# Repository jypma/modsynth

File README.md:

# Eurorack modules collection

This repository contains a collection of eurorack module open hardware designs. It is a combination of designs found elsewhere (with references where relevant), and designs by me.

All schematics and boards are in Kicad format, and schematics, board and gerber exports are automated using KiBot and docker (see [export.sh](export.sh)).

## Modules

The following modules are available:

* A [AS3340-based oscillator](AS3340-VCO) designed by me (based on a combination of earlier designs from the internet)
* A [PT2399-based delay](PT2399-Delay) designed by me (based on a combination of earlier designs from the internet)
- A [Dual 4-channel mixer](DualMixer) module designed by me (based on basic opamp mixer essentials)
- A [Quad Attenuverter](QuadAttenuverter) with offset, based on an internet design
- [Ornament & Crime](OrnamentCrime), a well-known open hardware design
- Ray Wilson's  [Dual-VCA](RayWilson-Dual-VCA) as originally designed by Gerbrand Sterrenburg
- [Roland System 100 ADSR](SCM-140-ADSR) as originally designed by Gerbrand Sterrenburg
- The YUSynth [Steiner VCF](Steiner-VCF) as originally designed by Gerbrand Sterrenburg
- Music Thing Modular's [Turing Machine](TuringMachine), a well-known open hardware design

## Utilities

- A 16-bin [DIP to SOIC](adapter-soic16) adapter board (to mount SOIC chips on DIP sockets)
- A [Power distribution board](power-board) for eurorack modules

## Combined bill of material and shopping list

I'm maintaining a merged [bill of material](bom.org) for all modules, with component lists in stock at time of writing.

The only exception is the Teensy 3.0 / 3.1 / 3.2 required for _Ornament & Crime_. Those are impossible to find at the moment (I happen to have some, hence it's on the list).

# Generating BOM, gerbers, and pictures

The script `export.sh` in the root of the project will generate or update the artifacts in the  `export/` directory, such as BOMs, gerber files, packages, and various documentation pictures. Most of these files are not version-controlled (but those linked from the markdown documentation are).

Whenever changing a schematic, the export script will update the relevant pictures and artifacts. Re-exporting the same schematic will result in the same picture, so `git` plays nice with this.

## Link for simulation of triangle to sine converter

[here](https://falstad.com/circuit/circuitjs.html?ctz=CQAgjCAMB0l3BWK0AckDMYwE4As3sA2SQgdgCYFsQFIaa6EBTAWiwCgAlEXOEciiHTpC-QXXQ8+SOrOgJ2YUrh7pyY9QjDqB6iGHh8YudJFIhOAewCuAOwAm7AO5S6u1TvHsATjXIoNPwD0BHU3cjh2AHMgoVDY9BQVWXYAFxpiQMJyFXc6CBZcaFJabWylCu1JGARCBDUwFFI8BF5cclEDOnsmADMAQ2sAG1TnDLdBUIC8nxBs3Jy5xbBcZPBDLiWVbQD5kCIoQ95wMMOasb2drfBVqAvF8kW9ylFIWcJj-wDSSFyUAIk2DeShUHwkIhAPxUwk66yM8gsTAAzgBLJGpfq2ADGTAuxxhc0+-zuLjB-GJz2JbxcUKEENpXzuvjI6kSoMEqwB-A2pMEbLmfIid3SaAm6lIhGm4nAIEKxUIYFCuHq2S0cFe8ioCAo+GU2CUyk6fB6A2GoxpkvJ31+VqZIBQYFEphUDqdlvCkRirqElu9vFkJPtjqENu9MxcYcEosCb18Eumi3j4Ey+Q23CTVyTBwDx20Z2QCgtAUzlsdKSL-ETlped141BQB0ZXWmxIgMFEbDAqBQrQ+P3IitwxHMMEg5Ewtcg1CwNudJz4c7b0A7Bmg6FIphyiuIpgII9g47bmzwuVq+1ujzWdFzpzkCm4WHi7kfOmOOfyt4Lx9uajoJ7in7HGwn7nA+iqshCL4+ly150MB+bnL4DadBK+zYHoqGpvAYzIeAqG4eGaEYUakDFphYzNnhJEtgCOGNlGaAxjhjHuP8bhvsx7F0M8izUpC1aLEkCbJDhuDCfaYkhiJEaSXOuFzrG9qMf6Sngq8cKRBGjEEvJNpvF6yl8GxHhnLMBgPK2pE0YcXSaesxJNgYfy0S45nOXC1mKVgQpKJ0ET5Jh4C0HZ3kBZ0TlUYGM7bKh0W2nx2h8L584SHp0T2cEPlWQBpmudlv7gBFBVvAA8ilUknLJel3NwLI8JJdViQGsGynmzXyGMTX8GeXWXoGvWLFMlbSbEfVDTMlgZDwRwoIQRrIG29DNUIcyHE67BAA)

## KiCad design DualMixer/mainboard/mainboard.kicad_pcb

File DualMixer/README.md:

# Dual 4-channel mixer

Based off a variety of simple opamp circuits, with the following design goals:

- 4 inputs per mixer
- Individual buffers for each input, to limit cross-talk between connected oscillators
- As close to unity output when one input connected and fully opened (hence, output A can be connected to input B1 for a 7-channel mixer)
- Peak LED for each output

## Main board

### Schematic

### PCB

## IO Board

### Schematic

### PCB

## Face plate

# Simulation

Simulate this circuit on [circuitjs](https://falstad.com/circuit/circuitjs.html?ctz=CQAgjCAMB0l3BWEAOM0CcAmSAWMA2SAdn3xLCQUhEuoQFMBaMMAKB0nRB3xxAGZsNQgKH8o0fCGb9omHOhyYE-fkXSQw6FhMiZ+YeEeN6orAEo0wmEJmTIrNzERvVqHcK6gSEFxwIQbBGsBfAc3bmpmLzdoX0t+XAEk+WpEvmoIQzgab1jfAHdkvnTuXmKzIp4S-ikcQQFayu4G1TqG+tdWKo6GhBIWrqL+9qCBwTdumnGhBBEJswAnaakFshsFtMS4PyJA0Ic9jeQM7w9ovJ9d-dKj23tLjxCImF8OLiIktpQc7-EYKQyaAuQjITAETDoBDIIiqXT6bImYxDECfEpCdaiSbLZCtJq4mx4KSZDjwVg4joEFAddDE7ifHYAc2phNpLP8kyKBMaUmQvyakCm3KJIDCDhFgqKYu4VOl-H2ktFD3lNjRARR3O+yDZ30FAHkUDqmlgHLqzAATdlahrOJzgAByeBwyCFNpc7Ow4VdTkgDm0Pq9AGMQP7bL6QyFbd40EjY2AmEQaJINPoYRQ4NYwOFYJpySGBp781Io9RMNgyUVQ4X0AXw4LmVX3VWHpMGwWmwWW2Z3uA4A4tDYWEkB+AJID9BgFIQs2B+Cd1ImYHoDLHkWZLIY5uARJupGAcKd3JkYlcN5At2W+LvbB4Iudnnk4lNsg5q7Wvct0FhwAMTT+6YiOyft+YC-t+bKZMYrANnY-6GnuAzYuAhhXiBWaoV4ZY7BCyEnOAIHyP2342Oa9AAGYAIYAK4ADYAC6MDR9CWhALywGwzLWM6+GDoRN4vHmIzcGymJTmcDKKpiazumJ9YrMJUgIAeCl5NB8lKXwGk0MpSFCVpmJae4EmCQMCDfgZ35GWSzJ6d+WlmTEUyiSJ7qGU5rnKRZKIvnBX6DohrAAPa2OIrHcMgpBhhIYVXiUth0pgqysEAA)

# Notes for boards v1 (Obsolete)

The level pots go in the wrong direction. Fix: Mount I/O board the wrong way, and connect the unconnected top left pin of the dual header row to its right sibling(ground). This will reverse the A/B output LEDs, but that's fine.

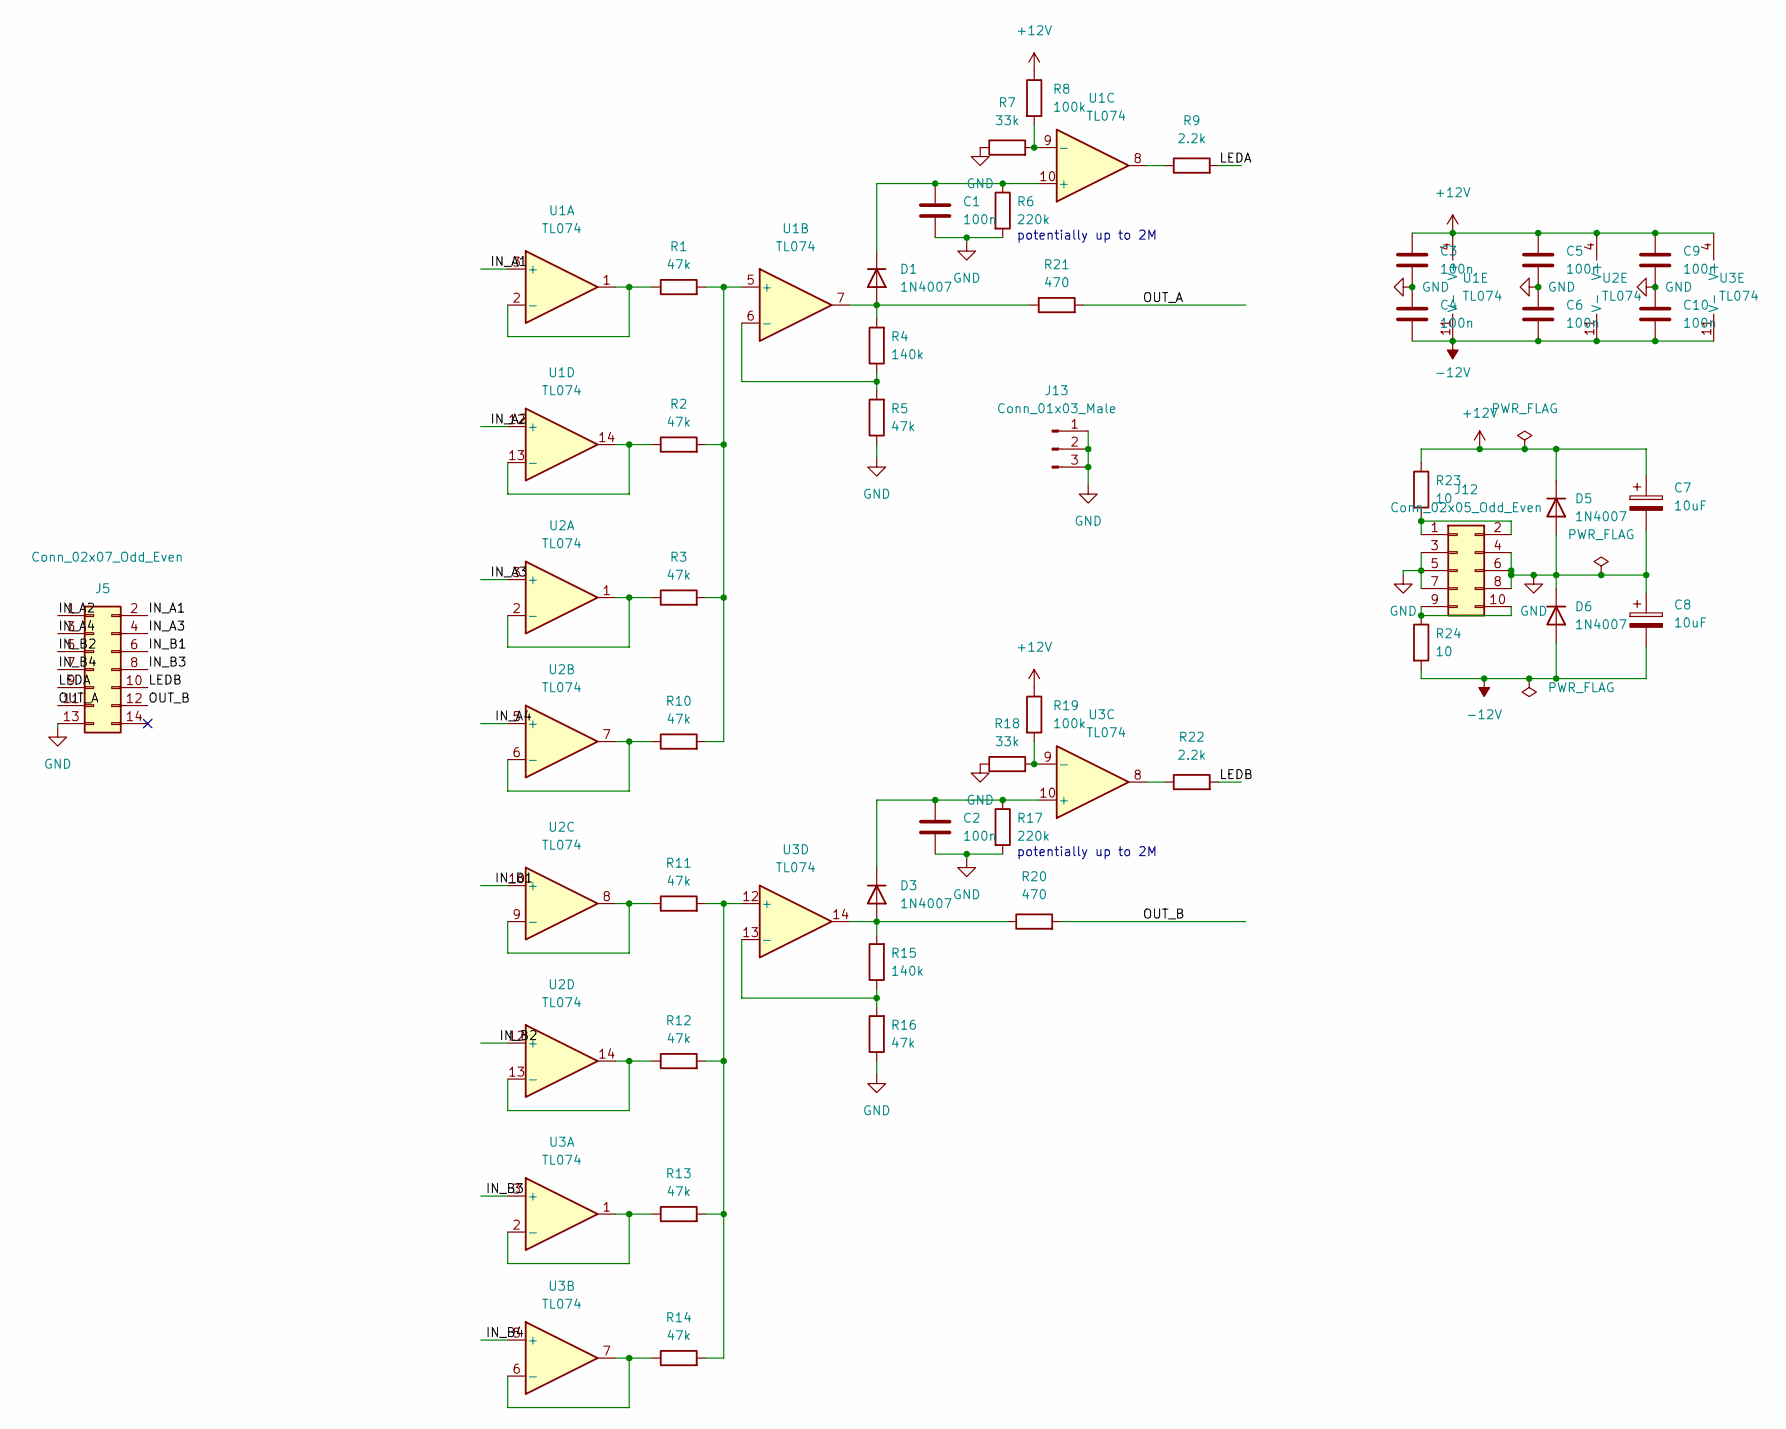
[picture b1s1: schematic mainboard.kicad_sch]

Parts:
C1, C2, C3, C4, C5, C6, C9, C10: 100n; C_0603_1608Metric_Pad1.08x0.95mm_HandSolder
C7, C8: 10uF; CP_Radial_D5.0mm_P2.50mm
D1, D3, D5, D6: 1N4007; D_DO-41_SOD81_P7.62mm_Horizontal
J5: Conn_02x07_Odd_Even; PinHeader_2x07_P2.54mm_Vertical
J12: Conn_02x05_Odd_Even; PinHeader_2x05_P2.54mm_Vertical
J13: Conn_01x03_Male; PinHeader_1x03_P2.54mm_Vertical
R1, R2, R3, R5, R10, R11, R12, R13, R14, R16: 47k; R_0603_1608Metric_Pad0.98x0.95mm_HandSolder
R4, R15: 140k; R_0603_1608Metric_Pad0.98x0.95mm_HandSolder
R6, R17: 220k; R_0603_1608Metric_Pad0.98x0.95mm_HandSolder
R7, R18: 33k; R_0603_1608Metric_Pad0.98x0.95mm_HandSolder
R8, R19: 100k; R_0603_1608Metric_Pad0.98x0.95mm_HandSolder
R9, R22: 2.2k; R_0603_1608Metric_Pad0.98x0.95mm_HandSolder
R20, R21: 470; R_0603_1608Metric_Pad0.98x0.95mm_HandSolder
R23, R24: 10; R_0603_1608Metric_Pad0.98x0.95mm_HandSolder
U1, U2, U3: TL074; SO-14_3.9x8.65mm_P1.27mm

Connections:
+12V: C3.1, C5.1, C7.1, C9.1, D5.1 (K), R8.1, R19.1, R23.1, U1.4 (V+), U2.4 (V+), U3.4 (V+)
-12V: C4.2, C6.2, C8.2, C10.2, D6.2 (A), R24.2, U1.11 (V-), U2.11 (V-), U3.11 (V-)
/IN_A1: J5.2, U1.3 (+)
/IN_A2: J5.1, U1.12 (+)
/IN_A3: J5.4, U2.3 (+)
/IN_A4: J5.3, U2.5 (+)
/IN_B1: J5.6, U2.10 (+)
/IN_B2: J5.5, U2.12 (+)
/IN_B3: J5.8, U3.3 (+)
/IN_B4: J5.7, U3.5 (+)
/LEDA: J5.9, R9.2
/LEDB: J5.10, R22.2
/OUT_A: J5.11, R21.2
/OUT_B: J5.12, R20.2
GND: C1.2, C2.2, C3.2, C4.1, C5.2, C6.1, C7.2, C8.1, C9.2, C10.1, D5.2 (A), D6.1 (K), J5.13, J12.3, J12.4, J12.5, J12.6, J12.7, J12.8, J13.1, J13.2, J13.3, R5.1, R6.2, R7.1, R16.1, R17.2, R18.1
unnamed: D1.2 (A), R4.2, R21.1, U1.7
unnamed: C1.1, D1.1 (K), R6.1, U1.10 (+)
unnamed: D3.2 (A), R15.2, R20.1, U3.14
unnamed: C2.1, D3.1 (K), R17.1, U3.10 (+)
unnamed: J12.1, J12.2, R23.2
unnamed: J12.9, J12.10, R24.1
unnamed: R9.1, U1.8
unnamed: R22.1, U3.8
unnamed: R1.1, U1.1, U1.2 (-)
unnamed: R1.2, R2.2, R3.2, R10.2, U1.5 (+)
unnamed: R4.1, R5.2, U1.6 (-)
unnamed: R7.2, R8.2, U1.9 (-)
unnamed: R2.1, U1.13 (-), U1.14
unnamed: R3.1, U2.1, U2.2 (-)
unnamed: R10.1, U2.6 (-), U2.7
unnamed: R11.1, U2.8, U2.9 (-)
unnamed: R12.1, U2.13 (-), U2.14
unnamed: R13.1, U3.1, U3.2 (-)
unnamed: R14.1, U3.6 (-), U3.7
unnamed: R18.2, R19.2, U3.9 (-)
unnamed: R11.2, R12.2, R13.2, R14.2, U3.12 (+)
unnamed: R15.1, R16.2, U3.13 (-)

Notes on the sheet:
potentially up to 2M

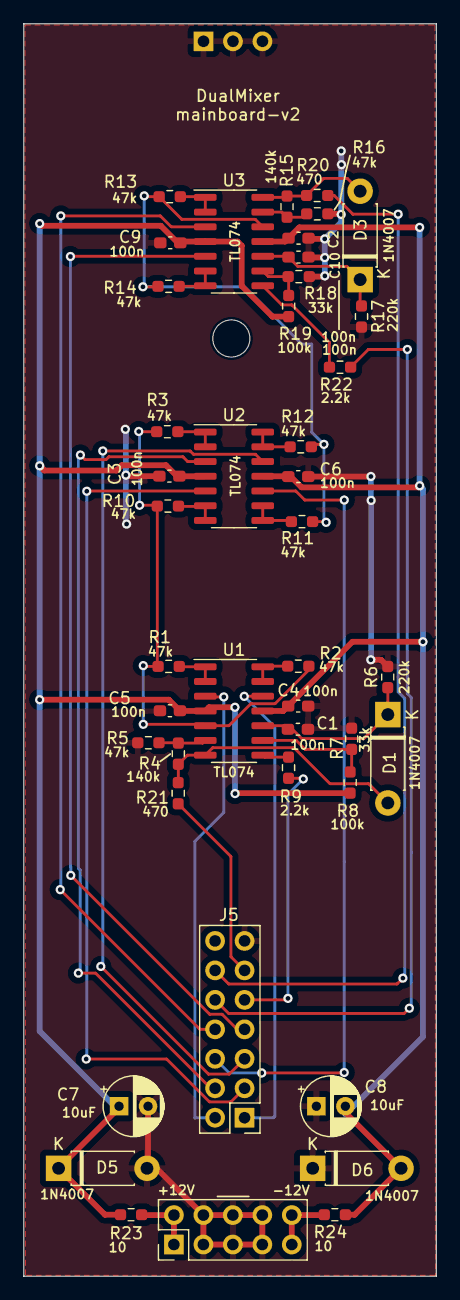
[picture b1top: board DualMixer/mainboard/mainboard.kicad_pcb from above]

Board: 2 copper layers, 35.6 x 107.9 mm, 44 parts (1 on the bottom side), 37 nets.

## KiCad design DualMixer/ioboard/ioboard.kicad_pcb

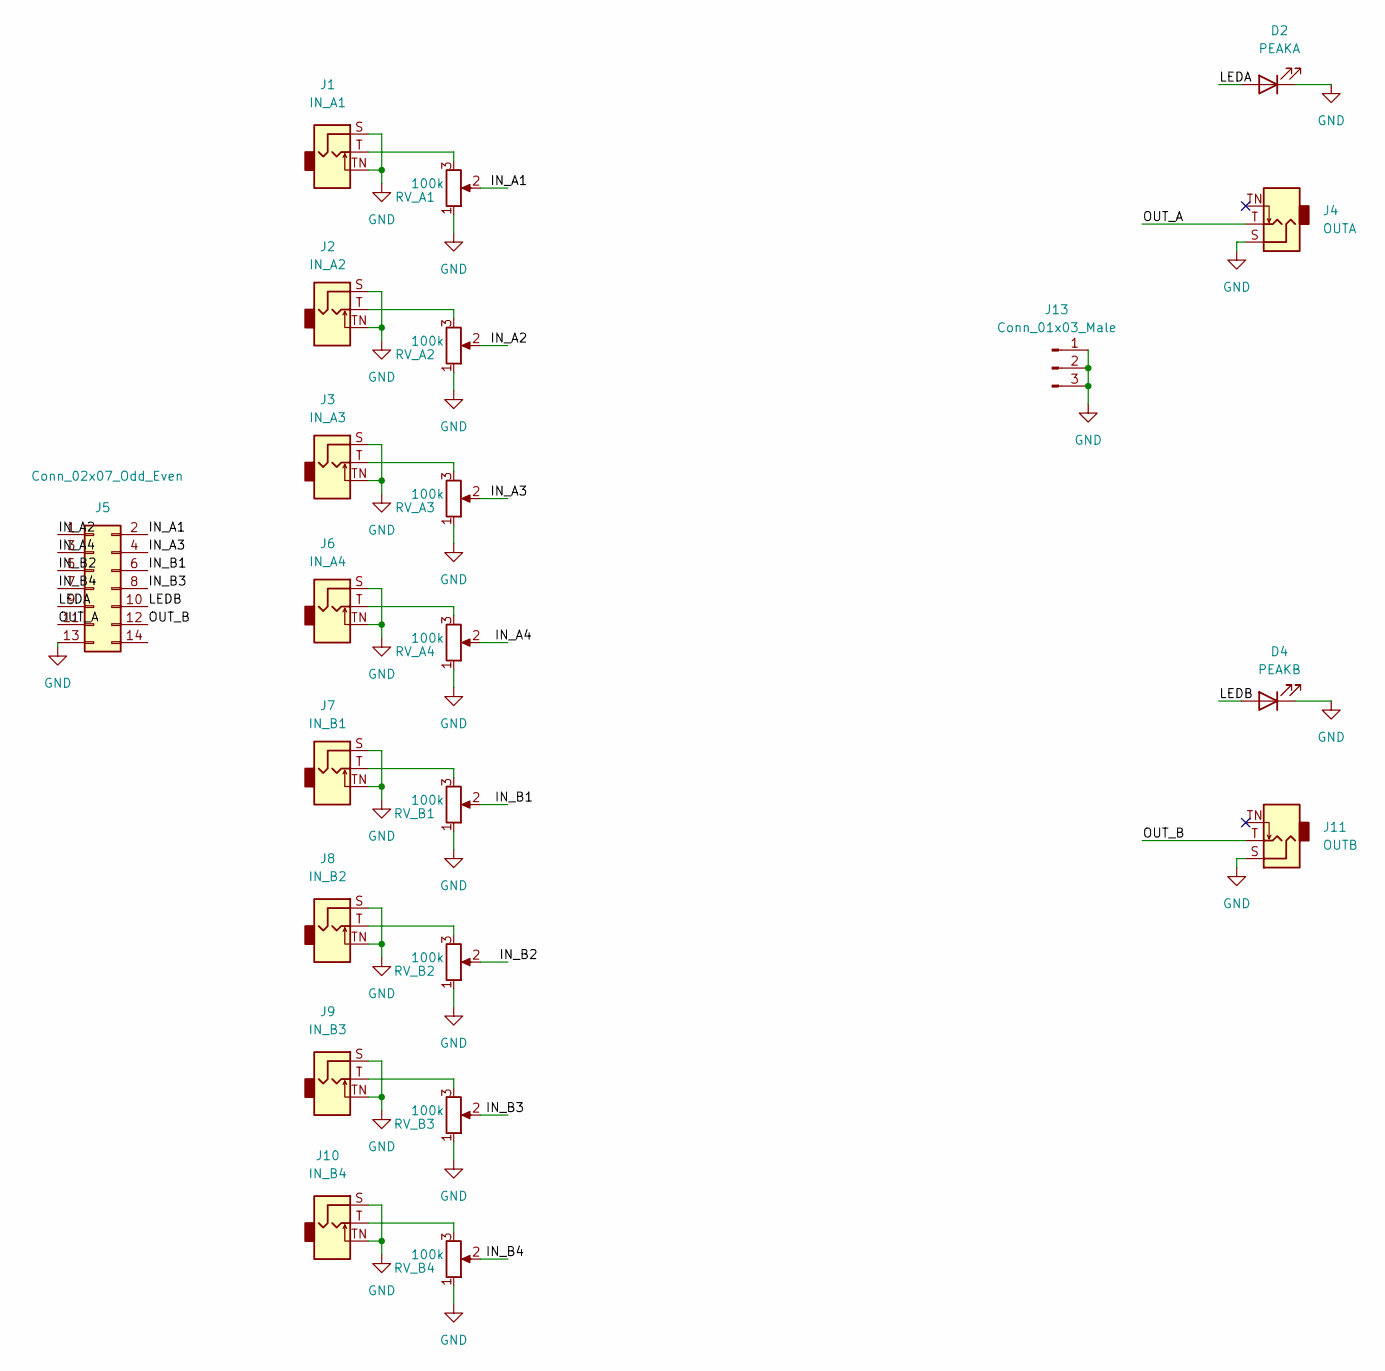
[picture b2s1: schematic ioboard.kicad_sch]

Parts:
D2: PEAKA; LED_D3.0mm
D4: PEAKB; LED_D3.0mm
J1: IN_A1; Jack_3.5mm_QingPu_WQP-PJ398SM_Vertical_CircularHoles
J2: IN_A2; Jack_3.5mm_QingPu_WQP-PJ398SM_Vertical_CircularHoles
J3: IN_A3; Jack_3.5mm_QingPu_WQP-PJ398SM_Vertical_CircularHoles
J4: OUTA; Jack_3.5mm_QingPu_WQP-PJ398SM_Vertical_CircularHoles
J5: Conn_02x07_Odd_Even; PinHeader_2x07_P2.54mm_Vertical
J6: IN_A4; Jack_3.5mm_QingPu_WQP-PJ398SM_Vertical_CircularHoles
J7: IN_B1; Jack_3.5mm_QingPu_WQP-PJ398SM_Vertical_CircularHoles
J8: IN_B2; Jack_3.5mm_QingPu_WQP-PJ398SM_Vertical_CircularHoles
J9: IN_B3; Jack_3.5mm_QingPu_WQP-PJ398SM_Vertical_CircularHoles
J10: IN_B4; Jack_3.5mm_QingPu_WQP-PJ398SM_Vertical_CircularHoles
J11: OUTB; Jack_3.5mm_QingPu_WQP-PJ398SM_Vertical_CircularHoles
J13: Conn_01x03_Male; PinHeader_1x03_P2.54mm_Vertical
RV_A1, RV_A2, RV_A3, RV_A4: 100k; Potentiometer_Alps_RK09K_Single_Vertical
RV_B1, RV_B2, RV_B3, RV_B4: 100k; Potentiometer_Alps_RK09K_Single_Vertical

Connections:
/IN_A1: J5.2, RV_A1.2
/IN_A2: J5.1, RV_A2.2
/IN_A3: J5.4, RV_A3.2
/IN_A4: J5.3, RV_A4.2
/IN_B1: J5.6, RV_B1.2
/IN_B2: J5.5, RV_B2.2
/IN_B3: J5.8, RV_B3.2
/IN_B4: J5.7, RV_B4.2
/LEDA: D2.2 (A), J5.9
/LEDB: D4.2 (A), J5.10
/OUT_A: J4.T, J5.11
/OUT_B: J5.12, J11.T
GND: D2.1 (K), D4.1 (K), J1.S, J1.TN, J2.S, J2.TN, J3.S, J3.TN, J4.S, J5.13, J6.S, J6.TN, J7.S, J7.TN, J8.S, J8.TN, J9.S, J9.TN, J10.S, J10.TN, J11.S, J13.1, J13.2, J13.3, RV_A1.1, RV_A2.1, RV_A3.1, RV_A4.1, RV_B1.1, RV_B2.1, RV_B3.1, RV_B4.1
unnamed: J1.T, RV_A1.3
unnamed: J2.T, RV_A2.3
unnamed: J3.T, RV_A3.3
unnamed: J6.T, RV_A4.3
unnamed: J7.T, RV_B1.3
unnamed: J8.T, RV_B2.3
unnamed: J9.T, RV_B3.3
unnamed: J10.T, RV_B4.3

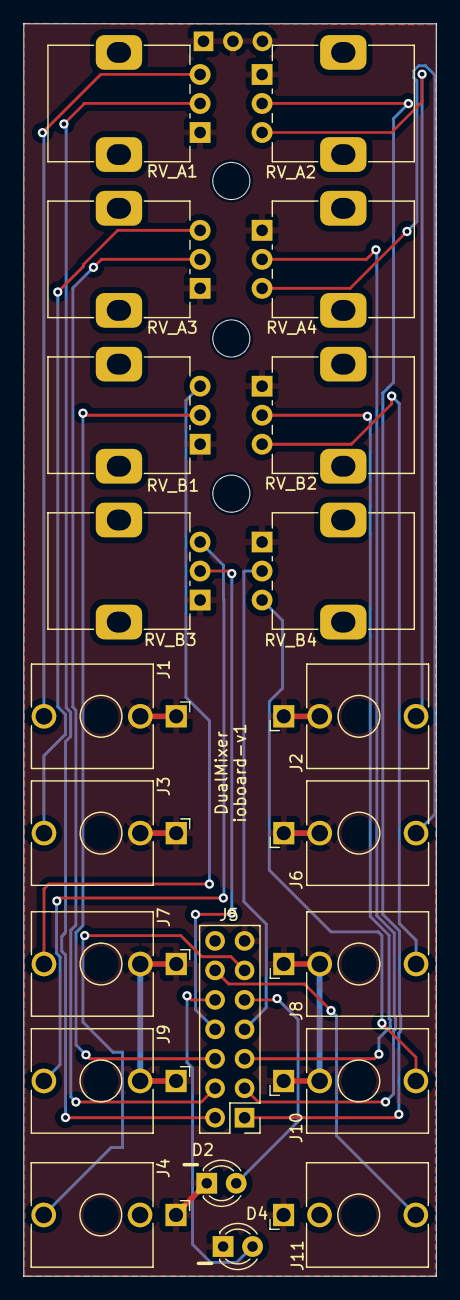
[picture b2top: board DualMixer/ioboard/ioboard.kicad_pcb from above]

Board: 2 copper layers, 35.6 x 107.9 mm, 22 parts (1 on the bottom side), 21 nets.

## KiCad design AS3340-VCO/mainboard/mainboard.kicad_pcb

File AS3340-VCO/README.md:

# AS3340 VCO

This design is a VCO based on the AS3340 chip, built up from a combination of designs found on the internet, resulting in the following features:
- Compact size
- Octave selector
- Holds tuning over time and temperature
* Precise finetune by note
* The usual linear FM, exponential FM and PWM inputs

## Main board

### Schematic

### PCB

## IO Board

### Schematic

### PCB

## Face plate

# Calibration
- Set to lowest octave
- Tune knob to lowest (1)
- Turn off LFO mode
- Set PWM to middle
- Connect V meter between GND and 1V
- Tweak RV_1V so we get 1.000V
- Connect V meter between GND and 7V
- Tweak RV_7V so we get about 7V
- Connect mV meter between TP1 and TP2
- Tweak RV_TEMPCO until voltage is 0V
- Put in JP1 to get a stable frequency
- Observe the triangle or square output
- Tweak RV_REF_PITCH_C6 until pitch is C6 (1046.5 Hz)
- Observe the sine output
- Tweak RV_OFFSET so that the middle value is 0V
- Tweak RV_SYM and RV_ROUND so the sine looks good
- Remove JP1
- Apply +5.000V CV
- Tweak RV_REFIND_C6 until pitch is again C6 (1046.5 Hz)
- Applu 0.000V CV
- Tweak RV_SCALE until pitch is 32.7Hz
- Connect V meter between GND and 1V
- Tweak RV_1V so we get 1.000V (TODO: figure out why this drifts)
- Connect V meter between GND and 7V
- Set to octave 6
- Tweak RV_7V until pitch is again C6 (1046.5 Hz)

# Old notes on advanced tuning schematic

## Tune towards C6
- 1M8: max ~800Hz
- 1M6: max ~910Hz
- 1M3: Spot on.
- Option: Replace 1M8 with 1M + 1M trimmer. But probably just a 0603 pad is fine too, we'll replace it with a fixed value for the main cap we end up using.

- Add an LFO switch, which adds a capacitor in parallel to the 1nF main cap.
  * normal labels: C1 through C9
  * 470 nF -> x labels:   13s   6.5s    3.2s    1.5s     0.78s      0.38s    0.19s   0.094s

- Octave switch goes from 0V to 7V (8 position switch, 7x10k 0.1% between the 8 positions. Make 7V with a TL431, R1 is 10k, R1 is 10k + 10k pot, 1k series resistor, plus 100nF bypass). Test point at +5V.
- Need a buffer opamp after the octave switch, even with the TL431 in front. TL072 with +12/-12V supply.

- Fine tune goes from 0V to 1V (take 7V from the octave switch, through 470k + 200k trimmer, to 100k pot).
- Need a buffer opamp after the fine tune as well.

- Put the high frequency tracking in the schematic, but don't need to initially populate.

# Errors in rev1 boards (obsolete)

- Mainboard silkscreen has the positions of values for R28 and R31 swapped. R28 should be 30k, and R31 should be 10k.
- Mainboard R41 should not have been to ground, it should be to -12V instead. Solder it to the left pad only (pointing left), and wire the other terminal to the bottom of R7 (which is -12V).
- IO board tune pot hole needs to be 7mm, to accommodate pots that are mounted

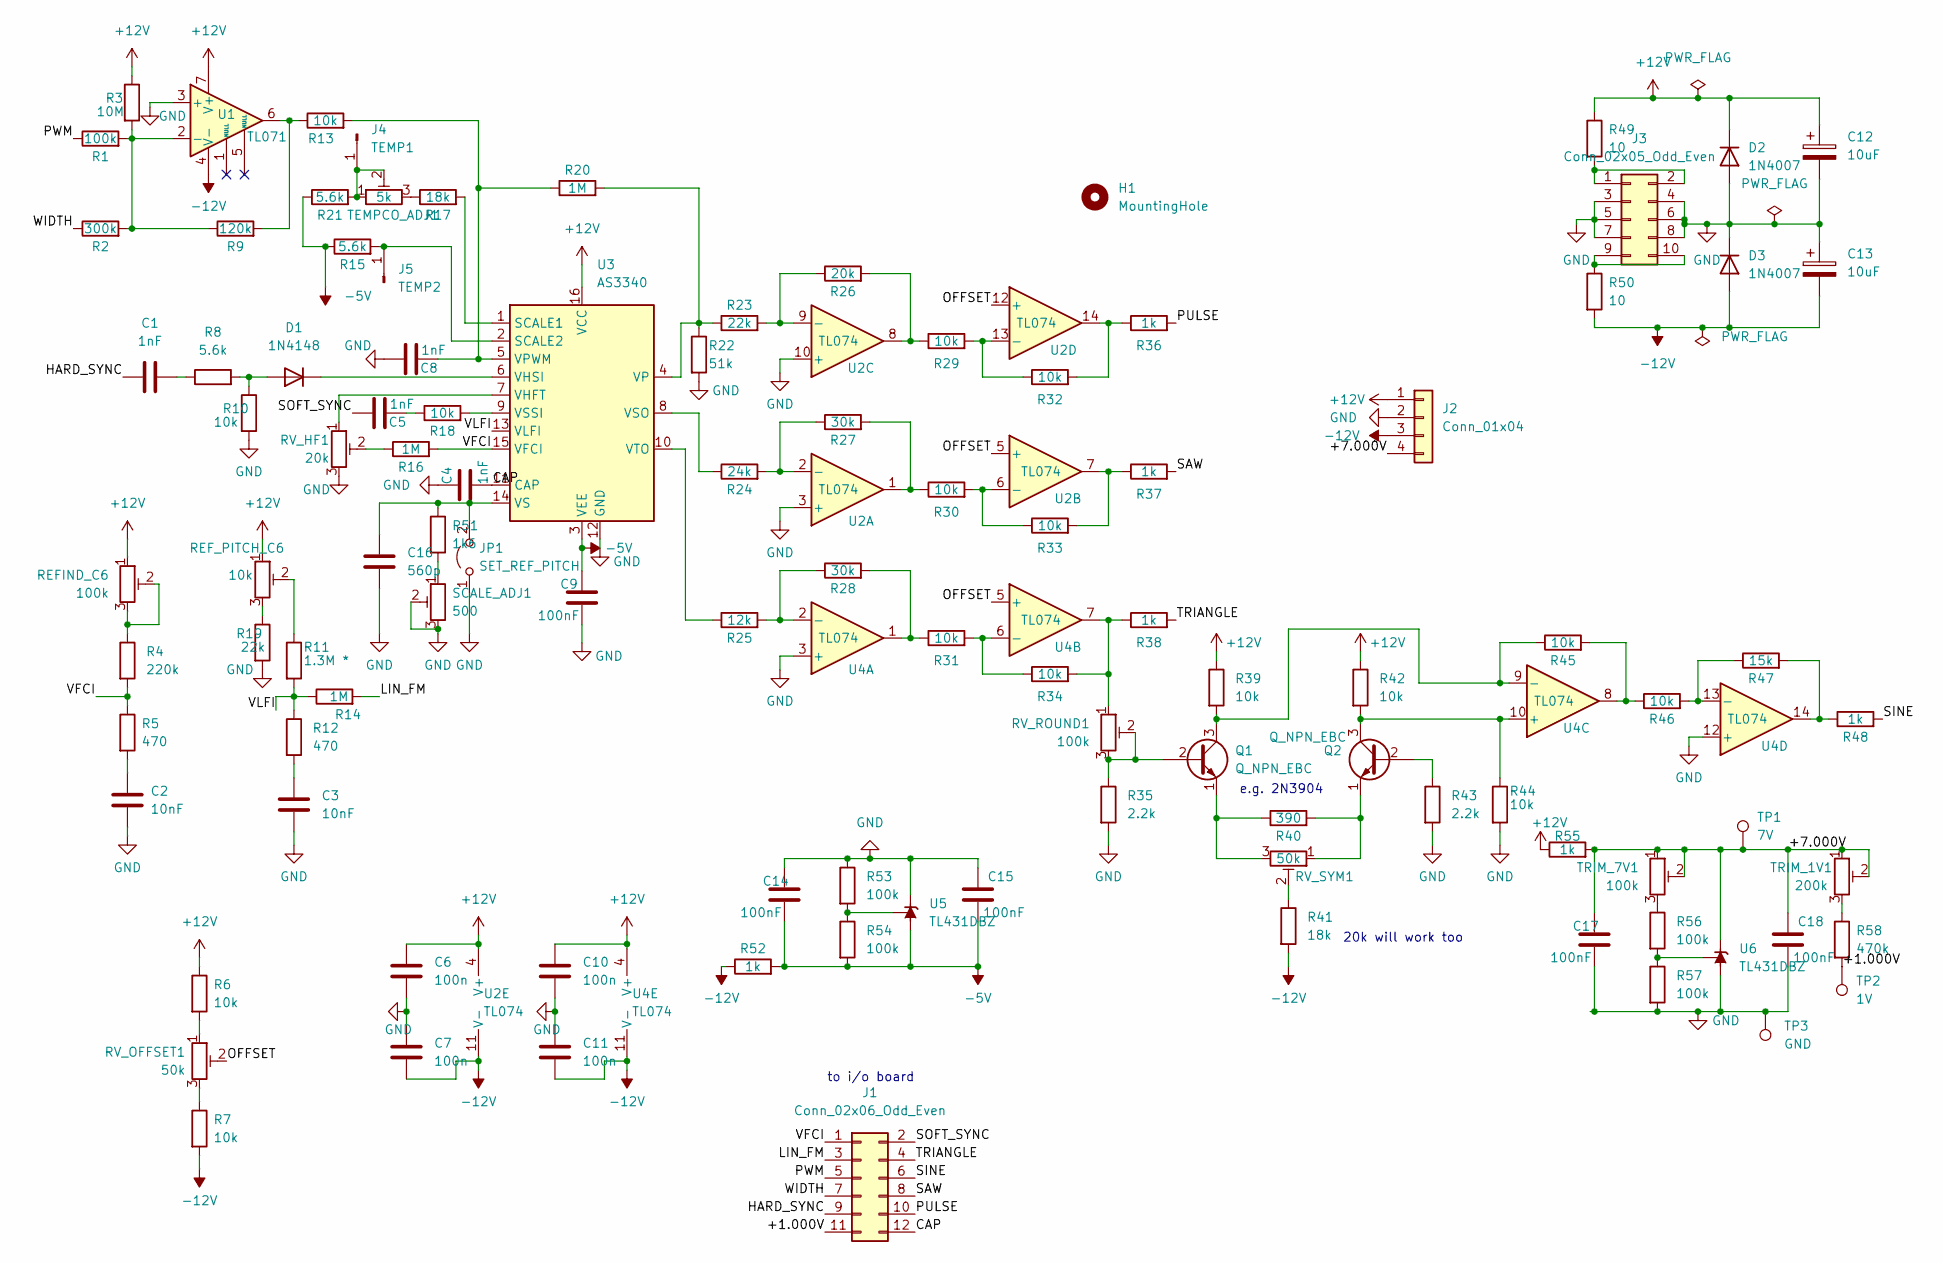
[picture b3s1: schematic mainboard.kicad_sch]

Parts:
C1, C5, C8: 1nF; C_0603_1608Metric_Pad1.08x0.95mm_HandSolder
C2, C3: 10nF; C_0603_1608Metric_Pad1.08x0.95mm_HandSolder
C4: 1nF; C_Rect_L7.0mm_W3.5mm_P5.00mm
C6, C7, C10, C11: 100n; C_0603_1608Metric_Pad1.08x0.95mm_HandSolder
C9, C14, C15, C17, C18: 100nF; C_0603_1608Metric_Pad1.08x0.95mm_HandSolder
C12, C13: 10uF; CP_Radial_D5.0mm_P2.50mm
C16: 560p; C_0603_1608Metric_Pad1.08x0.95mm_HandSolder
D1: 1N4148; D_DO-34_SOD68_P7.62mm_Horizontal
D2, D3: 1N4007; D_DO-41_SOD81_P7.62mm_Horizontal
H1: MountingHole; MountingHole_3.2mm_M3_NoCourt
J1: Conn_02x06_Odd_Even; PinHeader_2x06_P2.54mm_Vertical
J2: Conn_01x04; PinHeader_1x04_P2.54mm_Vertical
J3: Conn_02x05_Odd_Even; PinHeader_2x05_P2.54mm_Vertical
J4: TEMP1; PinHeader_1x01_P2.54mm_Vertical
J5: TEMP2; PinHeader_1x01_P2.54mm_Vertical
JP1: SET_REF_PITCH; PinHeader_1x02_P2.54mm_Vertical
Q1, Q2: Q_NPN_EBC; TO-92
R1, R53, R54, R56, R57: 100k; R_0603_1608Metric_Pad0.98x0.95mm_HandSolder
R2: 300k; R_0603_1608Metric_Pad0.98x0.95mm_HandSolder
R3: 10M; R_0603_1608Metric_Pad0.98x0.95mm_HandSolder
R4: 220k; R_0603_1608Metric_Pad0.98x0.95mm_HandSolder
R5, R12: 470; R_0603_1608Metric_Pad0.98x0.95mm_HandSolder
R6, R7, R10, R13, R18, R29, R30, R31, R32, R33, R34, R39, R42, R44, R45, R46: 10k; R_0603_1608Metric_Pad0.98x0.95mm_HandSolder
R8, R15, R21: 5.6k; R_0603_1608Metric_Pad0.98x0.95mm_HandSolder
R9: 120k; R_0603_1608Metric_Pad0.98x0.95mm_HandSolder
R11: 1.3M *; R_0603_1608Metric_Pad0.98x0.95mm_HandSolder
R14, R16, R20: 1M; R_0603_1608Metric_Pad0.98x0.95mm_HandSolder
R17, R41: 18k; R_0603_1608Metric_Pad0.98x0.95mm_HandSolder
R19, R23: 22k; R_0603_1608Metric_Pad0.98x0.95mm_HandSolder
R22: 51k; R_0603_1608Metric_Pad0.98x0.95mm_HandSolder
R24: 24k; R_0603_1608Metric_Pad0.98x0.95mm_HandSolder
R25: 12k; R_0603_1608Metric_Pad0.98x0.95mm_HandSolder
R26: 20k; R_0603_1608Metric_Pad0.98x0.95mm_HandSolder
R27, R28: 30k; R_0603_1608Metric_Pad0.98x0.95mm_HandSolder
R35, R43: 2.2k; R_0603_1608Metric_Pad0.98x0.95mm_HandSolder
R36, R37, R38, R48, R52, R55: 1k; R_0603_1608Metric_Pad0.98x0.95mm_HandSolder
R40: 390; R_0603_1608Metric_Pad0.98x0.95mm_HandSolder
R47: 15k; R_0603_1608Metric_Pad0.98x0.95mm_HandSolder
R49, R50: 10; R_0603_1608Metric_Pad0.98x0.95mm_HandSolder
R51: 1k6; R_0603_1608Metric_Pad0.98x0.95mm_HandSolder
R58: 470k; R_0603_1608Metric_Pad0.98x0.95mm_HandSolder
REFIND_C6: 100k; Potentiometer_Bourns_3266Y_Vertical
REF_PITCH_C6: 10k; Potentiometer_Bourns_3266Y_Vertical
RV_HF1: 20k; Potentiometer_Bourns_3266Y_Vertical
RV_OFFSET1: 50k; Potentiometer_Bourns_3266Y_Vertical
RV_ROUND1: 100k; Potentiometer_Bourns_3266Y_Vertical
RV_SYM1: 50k; Potentiometer_Bourns_3266Y_Vertical
SCALE_ADJ1: 500; Potentiometer_Bourns_3266Y_Vertical
TEMPCO_ADJ1: 5k; Potentiometer_Bourns_3266Y_Vertical
TP1: 7V; PinHeader_1x01_P2.54mm_Vertical
TP2: 1V; PinHeader_1x01_P2.54mm_Vertical
TP3: GND; PinHeader_1x01_P2.54mm_Vertical
TRIM_1V1: 200k; Potentiometer_Bourns_3266Y_Vertical
TRIM_7V1: 100k; Potentiometer_Bourns_3266Y_Vertical
U1: TL071; DIP-8_W7.62mm_Socket
U2, U4: TL074; SO-14_3.9x8.65mm_P1.27mm
U3: AS3340; DIP-16_W7.62mm_Socket
U5, U6: TL431DBZ; SOT-23

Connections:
+12V: C6.1, C10.1, C12.1, D2.1 (K), J2.1, R3.1, R6.1, R39.1, R42.1, R49.1, R55.1, REFIND_C6.1, REF_PITCH_C6.1, U1.7 (V+), U2.4 (V+), U3.16 (VCC), U4.4 (V+)
-5V: C9.1, C14.2, C15.2, R15.1, R21.1, R52.2, R54.2, U3.3 (VEE), U5.3 (A)
-12V: C7.2, C11.2, C13.2, D3.2 (A), J2.3, R7.2, R41.2, R50.2, R52.1, U1.4 (V-), U2.11 (V-), U4.11 (V-)
/+1.000V: J1.11, R58.2, TP2.1
/+7.000V: C17.1, C18.1, J2.4, R55.2, TP1.1, TRIM_1V1.1, TRIM_1V1.2, TRIM_7V1.1, TRIM_7V1.2, U6.1 (K)
/CAP: C4.1, J1.12, U3.11 (CAP)
/HARD_SYNC: C1.1, J1.9
/LIN_FM: J1.3, R14.2
/OFFSET: RV_OFFSET1.2, U2.5 (+), U2.12 (+), U4.5 (+)
/PULSE: J1.10, R36.2
/PWM: J1.5, R1.1
/SAW: J1.8, R37.2
/SINE: J1.6, R48.2
/SOFT_SYNC: C5.1, J1.2
/TRIANGLE: J1.4, R38.2
/VFCI: J1.1, R4.2, R5.1, R16.2, U3.15 (VFCI)
/VLFI: R11.2, R12.1, R14.1, U3.13 (VLFI)
/WIDTH: J1.7, R2.1
GND: C2.2, C3.2, C4.2, C6.2, C7.1, C8.1, C9.2, C10.2, C11.1, C12.2, C13.1, C14.1, C15.1, C16.2, C17.2, C18.2, D2.2 (A), D3.1 (K), J2.2, J3.3, J3.4, J3.5, J3.6, J3.7, J3.8, JP1.1 (A), R10.2, R19.2, R22.2, R35.2, R43.2, R44.2, R53.1, R57.2, RV_HF1.3, SCALE_ADJ1.2, SCALE_ADJ1.3, TP3.1, U1.3 (+), U2.3 (+), U2.10 (+), U3.12 (GND), U4.3 (+), U4.12 (+), U5.1 (K), U6.3 (A)
unnamed: C1.2, R8.1
unnamed: C2.1, R5.2
unnamed: C3.1, R12.2
unnamed: C5.2, R18.1
unnamed: D1.2 (A), R8.2, R10.1
unnamed: D1.1 (K), U3.6 (VHSI)
unnamed: J3.1, J3.2, R49.2
unnamed: J3.9, J3.10, R50.1
unnamed: J4.1, R21.2, TEMPCO_ADJ1.1, TEMPCO_ADJ1.2
unnamed: J5.1, R15.2, U3.2 (SCALE2)
unnamed: C16.1, JP1.2 (B), R51.1, U3.14 (VS)
unnamed: Q1.2 (B), R35.1, RV_ROUND1.2, RV_ROUND1.3
unnamed: Q1.3 (C), R39.2, R45.1, U4.9 (-)
unnamed: Q1.1 (E), R40.1, RV_SYM1.3
unnamed: Q2.2 (B), R43.1
unnamed: Q2.3 (C), R42.2, R44.1, U4.10 (+)
unnamed: Q2.1 (E), R40.2, RV_SYM1.1
unnamed: R4.1, REFIND_C6.2, REFIND_C6.3
unnamed: R6.2, RV_OFFSET1.1
unnamed: R7.1, RV_OFFSET1.3
unnamed: R11.1, REF_PITCH_C6.2
unnamed: R9.2, R13.1, U1.6
unnamed: R16.1, RV_HF1.2
unnamed: R17.1, TEMPCO_ADJ1.3
unnamed: R19.1, REF_PITCH_C6.3
unnamed: R26.2, R29.1, U2.8
unnamed: R27.2, R30.1, U2.1
unnamed: R28.2, R31.1, U4.1
unnamed: R32.2, R36.1, U2.14
unnamed: R33.2, R37.1, U2.7
unnamed: R34.2, R38.1, RV_ROUND1.1, U4.7
unnamed: R41.1, RV_SYM1.2
unnamed: R45.2, R46.1, U4.8
unnamed: R47.2, R48.1, U4.14
unnamed: R51.2, SCALE_ADJ1.1
unnamed: R56.1, TRIM_7V1.3
unnamed: R58.1, TRIM_1V1.3
unnamed: R1.2, R2.2, R3.2, R9.1, U1.2 (-)
unnamed: R24.2, R27.1, U2.2 (-)
unnamed: R30.2, R33.1, U2.6 (-)
unnamed: R23.2, R26.1, U2.9 (-)
unnamed: R29.2, R32.1, U2.13 (-)
unnamed: R17.2, U3.1 (SCALE1)
unnamed: RV_HF1.1, U3.7 (VHFT)
unnamed: R20.2, R22.1, R23.1, U3.4 (VP)
unnamed: C8.2, R13.2, R20.1, U3.5 (VPWM)
unnamed: R24.1, U3.8 (VSO)
unnamed: R18.2, U3.9 (VSSI)
unnamed: R25.1, U3.10 (VTO)
unnamed: R25.2, R28.1, U4.2 (-)
unnamed: R31.2, R34.1, U4.6 (-)
unnamed: R46.2, R47.1, U4.13 (-)
unnamed: R53.2, R54.1, U5.2 (REF)
unnamed: R56.2, R57.1, U6.2 (REF)

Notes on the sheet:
e.g. 2N3904
to i/o board
20k will work too

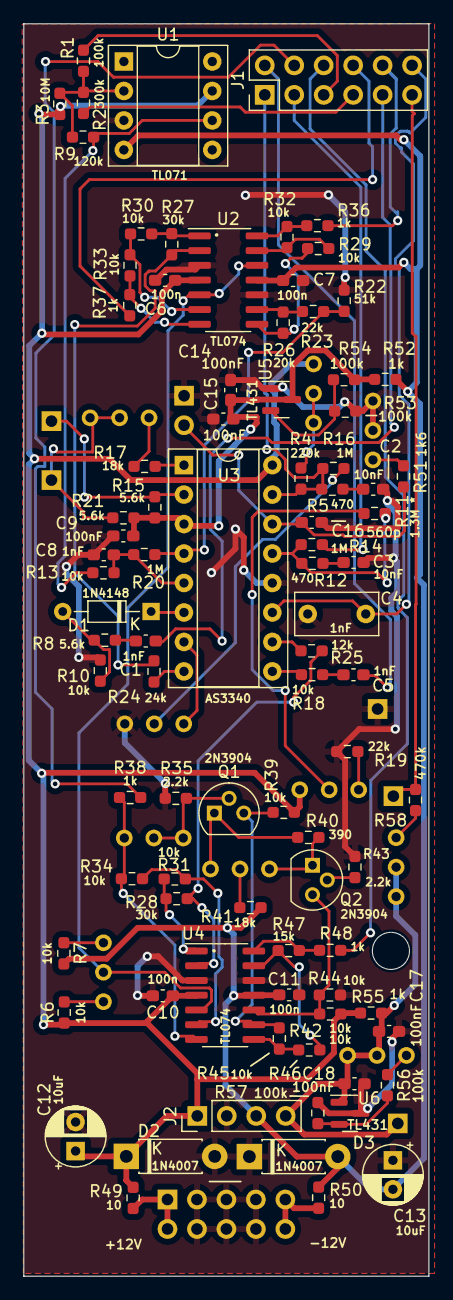
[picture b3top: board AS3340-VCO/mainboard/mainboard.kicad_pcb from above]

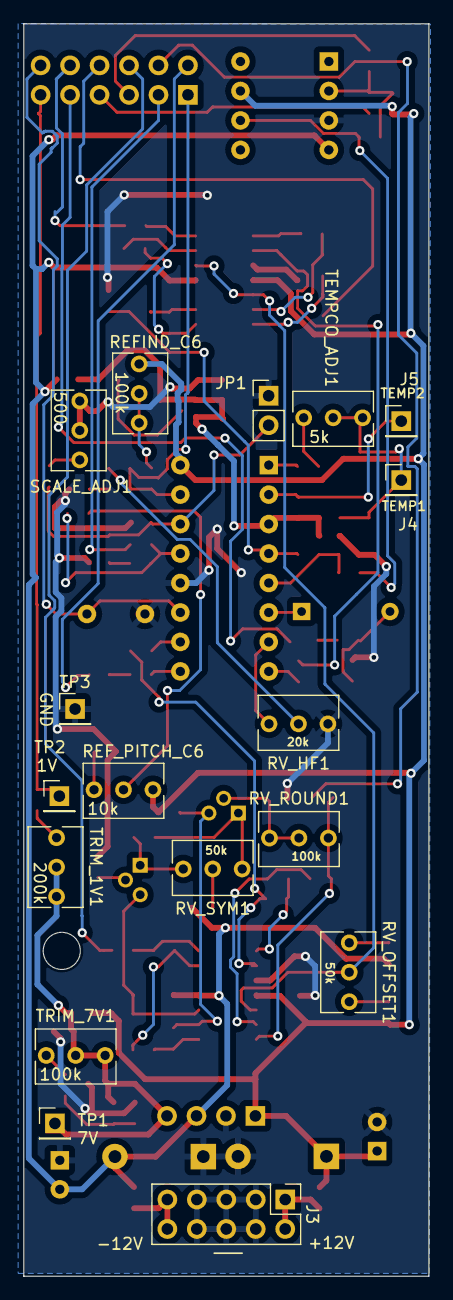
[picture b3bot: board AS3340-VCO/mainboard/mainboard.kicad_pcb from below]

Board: 2 copper layers, 34.9 x 107.9 mm, 107 parts (17 on the bottom side), 73 nets.

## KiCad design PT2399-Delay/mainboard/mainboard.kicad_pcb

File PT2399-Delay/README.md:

# PT2399 based delay

The schematic for this version is based on the [Encore](https://github.com/m0xpd/encore?tab=readme-ov-file) delay module. However, I've removed the VCA's and simplified the connections so it fits in a 20mm wide small module.

Also, the anti-latchup circuit was replaced with a more modern MOSFET, so the current source that sets the delay time is more easily regulated, independently from the latch-up circuit.

## Main board

### Schematic

### PCB

## IO Board

### Schematic

### PCB

## Face plate

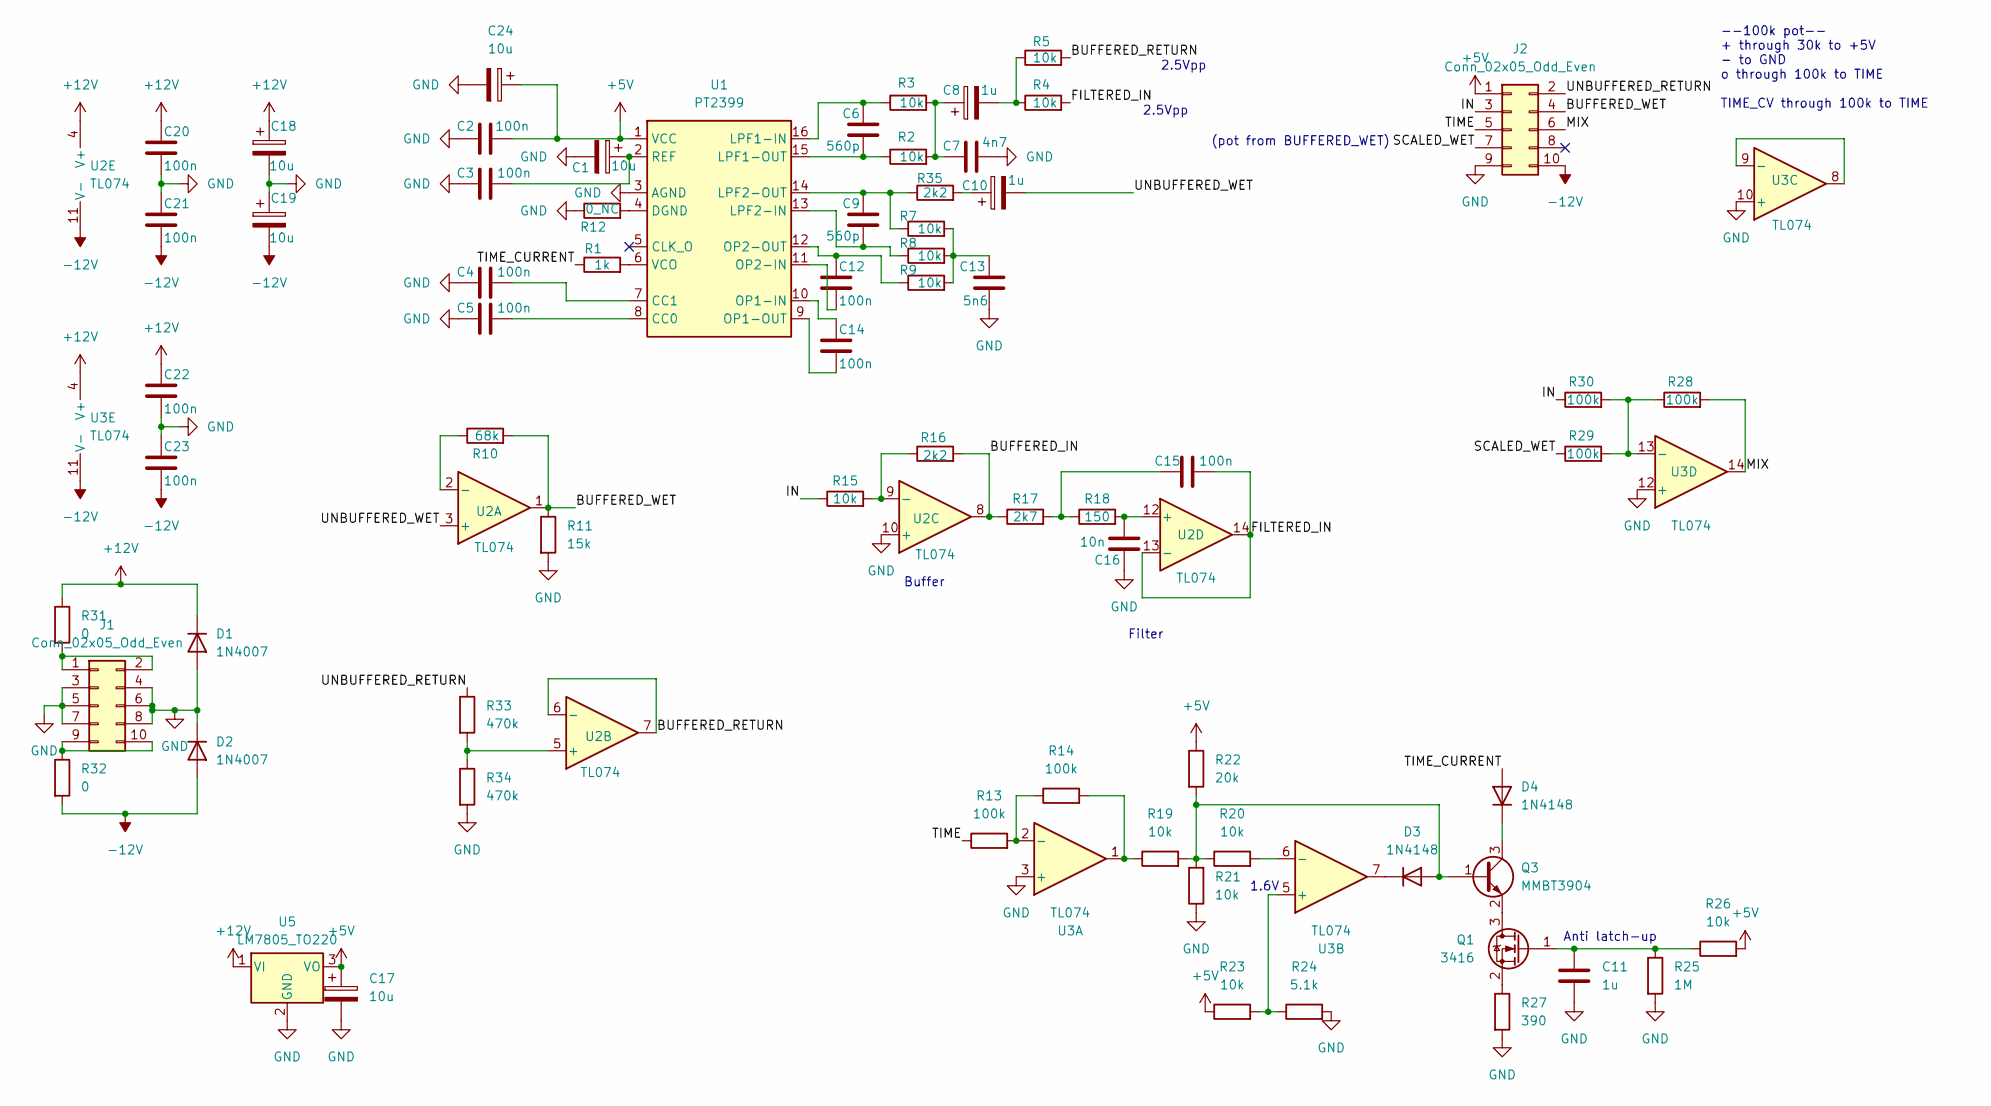
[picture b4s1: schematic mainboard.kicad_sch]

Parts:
C1: 10u; C_0603_1608Metric_Pad1.08x0.95mm_HandSolder
C2, C3, C4, C5, C12, C14, C15, C20, C21, C22, C23: 100n; C_0603_1608Metric_Pad1.08x0.95mm_HandSolder
C6, C9: 560p; C_0603_1608Metric_Pad1.08x0.95mm_HandSolder
C7: 4n7; C_0603_1608Metric_Pad1.08x0.95mm_HandSolder
C8, C10: 1u; CP_Radial_D4.0mm_P1.50mm
C11: 1u; C_0603_1608Metric_Pad1.08x0.95mm_HandSolder
C13: 5n6; C_0603_1608Metric_Pad1.08x0.95mm_HandSolder
C16: 10n; C_0603_1608Metric_Pad1.08x0.95mm_HandSolder
C17, C18, C19, C24: 10u; CP_Radial_D4.0mm_P1.50mm
D1, D2: 1N4007; D_DO-41_SOD81_P7.62mm_Horizontal
D3, D4: 1N4148; D_SOD-323_HandSoldering
J1, J2: Conn_02x05_Odd_Even; PinHeader_2x05_P2.54mm_Vertical
Q1: 3416; SOT-23
Q3: MMBT3904; SOT-23
R1: 1k; R_0603_1608Metric_Pad0.98x0.95mm_HandSolder
R2, R3, R4, R5, R7, R8, R9, R15, R19, R20, R21, R23, R26: 10k; R_0603_1608Metric_Pad0.98x0.95mm_HandSolder
R10: 68k; R_0603_1608Metric_Pad0.98x0.95mm_HandSolder
R11: 15k; R_0603_1608Metric_Pad0.98x0.95mm_HandSolder
R12: 0_NC; R_0603_1608Metric_Pad0.98x0.95mm_HandSolder
R13, R14, R28, R29, R30: 100k; R_0603_1608Metric_Pad0.98x0.95mm_HandSolder
R16, R35: 2k2; R_0603_1608Metric_Pad0.98x0.95mm_HandSolder
R17: 2k7; R_0603_1608Metric_Pad0.98x0.95mm_HandSolder
R18: 150; R_0603_1608Metric_Pad0.98x0.95mm_HandSolder
R22: 20k; R_0603_1608Metric_Pad0.98x0.95mm_HandSolder
R24: 5.1k; R_0603_1608Metric_Pad0.98x0.95mm_HandSolder
R25: 1M; R_0603_1608Metric_Pad0.98x0.95mm_HandSolder
R27: 390; R_0603_1608Metric_Pad0.98x0.95mm_HandSolder
R31, R32: 0; R_0603_1608Metric_Pad0.98x0.95mm_HandSolder
R33, R34: 470k; R_0603_1608Metric_Pad0.98x0.95mm_HandSolder
U1: PT2399; SOP-16_3.9x9.9mm_P1.27mm
U2, U3: TL074; SO-14_3.9x8.65mm_P1.27mm
U5: LM7805_TO220; TO-220-3_Vertical

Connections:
+5V: C2.2, C17.1, C24.1, J2.1, R22.1, R23.1, R26.2, U1.1 (VCC), U5.3 (VO)
+12V: C18.1, C20.1, C22.1, D1.1 (K), R31.1, U2.4 (V+), U3.4 (V+), U5.1 (VI)
-12V: C19.2, C21.2, C23.2, D2.2 (A), J2.10, R32.2, U2.11 (V-), U3.11 (V-)
/BUFFERED_IN: R16.2, R17.1, U2.8
/BUFFERED_RETURN: R5.2, U2.6 (-), U2.7
/BUFFERED_WET: J2.4, R10.2, R11.1, U2.1
/FILTERED_IN: C15.2, R4.2, U2.13 (-), U2.14
/IN: J2.3, R15.1, R30.1
/MIX: J2.6, R28.2, U3.14
/SCALED_WET: J2.7, R29.1
/TIME: J2.5, R13.1
/TIME_CURRENT: D4.2 (A), R1.1
/UNBUFFERED_RETURN: J2.2, R33.1
/UNBUFFERED_WET: C10.2, U2.3 (+); also elsewhere on the board
GND: C1.2, C2.1, C3.1, C4.1, C5.1, C7.2, C11.2, C13.2, C16.2, C17.2, C18.2, C19.1, C20.2, C21.1, C22.2, C23.1, C24.2, D1.2 (A), D2.1 (K), J1.3, J1.4, J1.5, J1.6, J1.7, J1.8, J2.9, R11.2, R12.1, R21.1, R24.2, R25.2, R27.2, R34.2, U1.3 (AGND), U2.10 (+), U3.3 (+), U3.10 (+), U3.12 (+), U5.2 (GND); also elsewhere on the board
unnamed: C7.1, C8.1, R2.2, R3.2
unnamed: C8.2, R4.1, R5.1
unnamed: C10.1, R35.2
unnamed: C13.1, R7.2, R8.2, R9.2
unnamed: C15.1, R17.2, R18.1
unnamed: D3.2 (A), Q3.1 (B), R19.2, R20.1, R21.2, R22.2
unnamed: D3.1 (K), U3.7
unnamed: D4.1 (K), Q3.3 (C)
unnamed: J1.1, J1.2, R31.2
unnamed: J1.9, J1.10, R32.1
unnamed: Q1.3 (D), Q3.2 (E)
unnamed: C11.1, Q1.1 (G), R25.1, R26.1
unnamed: Q1.2 (S), R27.1
unnamed: R14.2, R19.1, U3.1
unnamed: C5.2, U1.8 (CC0)
unnamed: C4.2, U1.7 (CC1)
unnamed: R12.2, U1.4 (DGND)
unnamed: C6.1, R3.1, U1.16 (LPF1-IN)
unnamed: C6.2, R2.1, U1.15 (LPF1-OUT)
unnamed: C9.2, R8.1, U1.13 (LPF2-IN)
unnamed: C9.1, R7.1, R35.1, U1.14 (LPF2-OUT)
unnamed: C14.1, U1.10 (OP1-IN)
unnamed: C14.2, U1.9 (OP1-OUT)
unnamed: C12.2, U1.11 (OP2-IN)
unnamed: C12.1, R9.1, U1.12 (OP2-OUT)
unnamed: C1.1, C3.2, U1.2 (REF)
unnamed: R1.2, U1.6 (VCO)
unnamed: R10.1, U2.2 (-)
unnamed: R33.2, R34.1, U2.5 (+)
unnamed: R15.2, R16.1, U2.9 (-)
unnamed: C16.1, R18.2, U2.12 (+)
unnamed: R13.2, R14.1, U3.2 (-)
unnamed: R23.2, R24.1, U3.5 (+)
unnamed: R20.2, U3.6 (-)
unnamed: U3.8, U3.9 (-)
unnamed: R28.1, R29.2, R30.2, U3.13 (-)

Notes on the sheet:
Anti latch-up
1.6V
2.5Vpp
Buffer
--100k pot-- + through 30k to +5V - to GND o through 100k to TIME TIME_CV through 100k to TIME
(pot from BUFFERED_WET)
Filter
